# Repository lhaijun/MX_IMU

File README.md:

1. 代码优化：更合理稳定的代码组织结构为了优化数据读取、姿态解算和串口发送的代码结构，同时提升稳定性和可维护性，建议从以下几个方面入手：1.1 任务划分与优先级设计目前你使用 FreeRTOS 的定时器轮询方式，虽然简单，但可能导致任务耦合过高，且实时性难以保证。建议将功能模块拆分为独立的任务，利用 FreeRTOS 的多任务特性来提升代码模块化和稳定性。任务拆分建议：IMU 数据读取任务（高优先级）：负责从 ICM42688P 读取原始数据（加速度、角速度等）。建议使用 SPI/I2C 中断驱动的方式，避免轮询占用 CPU。读取频率可以根据 IMU 的采样率（如 100Hz 或 200Hz）设置。
姿态解算任务（中优先级）：接收 IMU 原始数据，进行姿态解算（如四元数或欧拉角）。可以利用 FreeRTOS 的队列（Queue）或信号量（Semaphore）从 IMU 任务获取数据，避免直接调用。
数据发送任务（低优先级）：负责将解算结果通过串口（UART）以 MAVLink 协议发送到上位机。可以使用另一队列接收姿态解算任务的数据。
命令处理任务（低优先级）：处理上位机通过 MAVLink 协议发送的参数调整命令，更新板载配置。

优先级设置：IMU 读取任务优先级最高，确保数据采集的实时性。
姿态解算次之，保证解算的及时性。
数据发送和命令处理优先级较低，因为串口通信和参数调整对实时性要求较低。

任务通信：使用 FreeRTOS 的 队列（Queue） 传递数据，例如：IMU 任务将原始数据放入队列，姿态解算任务从中读取。
姿态解算任务将结果放入另一个队列，供数据发送任务使用。

如果需要同步，使用 信号量（Semaphore） 或 事件标志（Event Group） 通知任务间状态。

1.2 替换定时器轮询为中断驱动IMU 数据读取：ICM42688P 支持数据就绪中断（Data Ready Interrupt）。建议配置中断引脚，当 IMU 数据准备好时触发中断，在中断服务函数（ISR）中读取数据并存入队列。这样可以避免轮询浪费 CPU 资源。
串口发送：使用 UART 的 DMA 模式发送 MAVLink 数据包，减少 CPU 干预。FreeRTOS 的任务只需将数据写入 DMA 缓冲区，硬件会自动完成发送。
姿态解算：姿态解算任务可以由事件触发（如队列中有新数据时运行），避免固定周期轮询。

1.3 代码模块化分离硬件驱动与应用逻辑：将 ICM42688P 的 SPI/I2C 驱动代码封装为独立模块（如 icm42688p.c/h），提供初始化、数据读取等接口。
姿态解算算法（如 Madgwick 或 Mahony 滤波）封装为单独模块（如 attitude.c/h），输入为 IMU 数据，输出为姿态数据。
MAVLink 协议处理封装为单独模块（如 mavlink_handler.c/h），负责打包和解析数据。

配置文件：将关键参数（如 IMU 采样率、滤波参数、串口波特率）集中在一个配置文件（如 config.h）中，方便上位机调整和代码维护。
错误处理：为每个模块添加错误检测和日志记录（如通过串口输出调试信息），便于调试和排查问题。

1.4 优化 FreeRTOS 资源使用任务栈大小：使用 FreeRTOS 的 uxTaskGetStackHighWaterMark 检查每个任务的栈使用情况，调整栈大小以节省内存。
队列长度：根据数据速率和任务调度频率，合理设置队列长度，避免队列满导致数据丢失。
调度器优化：确保任务调度频率与硬件性能匹配，避免任务抢占导致延迟。例如，IMU 采样率 100Hz，任务调度周期应与之同步。

1.5 示例代码结构以下是一个推荐的 FreeRTOS 任务组织示例：c

#include "FreeRTOS.h"
#include "task.h"
#include "queue.h"
#include "icm42688p.h"
#include "attitude.h"
#include "mavlink_handler.h"

// 队列句柄
QueueHandle_t imu_data_queue, attitude_data_queue;

// IMU 数据读取任务
void imu_read_task(void *pvParameters) {
    while (1) {
        // 假设通过中断触发读取
        imu_data_t data = icm42688p_read();
        xQueueSend(imu_data_queue, &data, portMAX_DELAY);
        vTaskDelay(pdMS_TO_TICKS(10)); // 100Hz
    }
}

// 姿态解算任务
void attitude_task(void *pvParameters) {
    imu_data_t imu_data;
    attitude_data_t attitude;
    while (1) {
        if (xQueueReceive(imu_data_queue, &imu_data, portMAX_DELAY)) {
            attitude = attitude_calculate(&imu_data);
            xQueueSend(attitude_data_queue, &attitude, portMAX_DELAY);
        }
    }
}

// 数据发送任务
void mavlink_send_task(void *pvParameters) {
    attitude_data_t attitude;
    while (1) {
        if (xQueueReceive(attitude_data_queue, &attitude, portMAX_DELAY)) {
            mavlink_send_attitude(&attitude);
        }
    }
}

void main(void) {
    // 初始化硬件和 FreeRTOS
    icm42688p_init();
    mavlink_init();
    
    // 创建队列
    imu_data_queue = xQueueCreate(10, sizeof(imu_data_t));
    attitude_data_queue = xQueueCreate(10, sizeof(attitude_data_t));
    
    // 创建任务
    xTaskCreate(imu_read_task, "IMU", 256, NULL, 3, NULL);
    xTaskCreate(attitude_task, "Attitude", 512, NULL, 2, NULL);
    xTaskCreate(mavlink_send_task, "MAVLink", 256, NULL, 1, NULL);
    
    // 启动调度器
    vTaskStartScheduler();
}

1.6 性能测试与验证实时性测试：使用逻辑分析仪或调试串口记录任务执行时间，确保 IMU 数据读取和姿态解算满足实时性要求。
稳定性测试：长时间运行系统，检查是否有内存泄漏或任务死锁。
数据一致性：验证上位机接收的 MAVLink 数据与板载解算结果一致。

2. 开源文档组织：GitHub 开源准备为了在 GitHub 上开源你的设计和代码，清晰的文档和项目结构是吸引用户和贡献者的关键。以下是建议的文档组织方式和内容：2.1 仓库结构

project_name/
├── docs/                     # 文档目录
│   ├── hardware/             # 硬件相关文档
│   ├── software/             # 软件相关文档
│   └── tutorials/            # 使用教程
├── firmware/                 # 固件代码
│   ├── src/                  # 源代码
│   ├── inc/                  # 头文件
│   └── lib/                  # 第三方库（如 FreeRTOS、MAVLink）
├── hardware/                 # 硬件设计文件
│   ├── schematic/            # 原理图（如 KiCad 文件）
│   ├── pcb/                  # PCB 布局
│   └── bom/                  # 物料清单
├── examples/                 # 示例代码或上位机代码
├── LICENSE                   # 开源许可证（如 MIT、Apache 2.0）
└── README.md                 # 项目主页

2.2 README.md 内容README 是项目的门面，需简洁但信息全面。建议包含以下内容：项目概述：简要介绍项目（STM32F405 + ICM42688P 的 IMU 系统，支持 MAVLink 协议）。
功能特性：IMU 数据读取（加速度、角速度）
姿态解算（四元数/欧拉角）
MAVLink 协议通信
FreeRTOS 实时系统

硬件要求：列出核心硬件（STM32F405、ICM42688P）及其连接方式。
软件依赖：STM32CubeIDE 或其他 IDE
FreeRTOS
MAVLink 库

快速开始：克隆仓库：git clone <repo_url>
硬件连接说明
编译和烧录固件步骤
上位机配置和运行

贡献指南：如何提交 Issue 或 Pull Request。
许可证：明确项目的开源许可证。
联系方式：可选，提供邮箱或社区链接。

2.3 文档内容硬件文档（docs/hardware/）：原理图和 PCB 设计说明（推荐使用 KiCad 或 Eagle）。
物料清单（BOM），包括元件型号和供应商链接。
硬件连接说明（如 SPI/I2C 引脚分配）。

软件文档（docs/software/）：代码架构说明（任务划分、模块功能）。
MAVLink 协议实现细节（支持的消息类型、参数调整流程）。
姿态解算算法说明（如 Madgwick 滤波的原理和参数）。

使用教程（docs/tutorials/）：固件烧录教程（使用 ST-Link 或其他工具）。
上位机配置和运行说明。
参数调整示例（如通过 MAVLink 修改滤波增益）。

API 文档（可选）：如果代码模块化程度高，可使用 Doxygen 生成 API 文档。

2.4 开源注意事项选择许可证：推荐 MIT 或 Apache 2.0，简单且适合硬件/软件开源。确保在仓库根目录添加 LICENSE 文件。
代码注释：确保代码有清晰的注释，尤其是关键模块（如 IMU 驱动、姿态解算）。
版本管理：使用 Git 提交规范（如 feat: add IMU driver），并定期发布版本（Releases）。
测试用例：提供简单的测试代码或脚本，帮助用户验证硬件和固件功能。
社区互动：在 README 中添加 GitHub Issues 模板，鼓励用户反馈问题或贡献代码。

2.5 示例 README 片段markdown

# STM32F405 + ICM42688P IMU Project

A FreeRTOS-based IMU system using STM32F405 and ICM42688P, with MAVLink protocol support for attitude calculation and data communication.

## Features
- High-frequency IMU data acquisition (100Hz+)
- Real-time attitude calculation (quaternion/Euler angles)
- MAVLink protocol for PC communication
- Configurable parameters via MAVLink

## Getting Started
1. Clone the repository:
   ```bash
   git clone https://github.com/yourusername/project_name

Connect STM32F405 and ICM42688P via SPI/I2C (see docs/hardware/).
Build and flash firmware using STM32CubeIDE.
Run the provided PC application to receive MAVLink data.

LicenseMIT License

---

### 3. 其他建议
- **硬件优化**：
  - 检查 ICM42688P 的电源和信号完整性，确保数据读取稳定。
  - 如果可能，添加外部晶振以提高 STM32F405 的时钟精度。
- **上位机完善**：
  - 在上位机中添加数据可视化功能（如姿态 3D 模型）。
  - 提供 MAVLink 参数调整的 GUI 界面，方便用户操作。
- **开源社区推广**：
  - 在 X 或其他技术社区分享你的项目，吸引开发者参与。
  - 考虑制作一个简单的演示视频，展示硬件运行效果。

---

### 总结
- **代码优化**：将功能拆分为 FreeRTOS 任务（IMU 读取、姿态解算、数据发送），使用中断驱动和队列通信，模块化代码结构。
- **文档组织**：在 GitHub 上创建清晰的目录结构，编写详细的 README 和模块化文档，选择合适的许可证。

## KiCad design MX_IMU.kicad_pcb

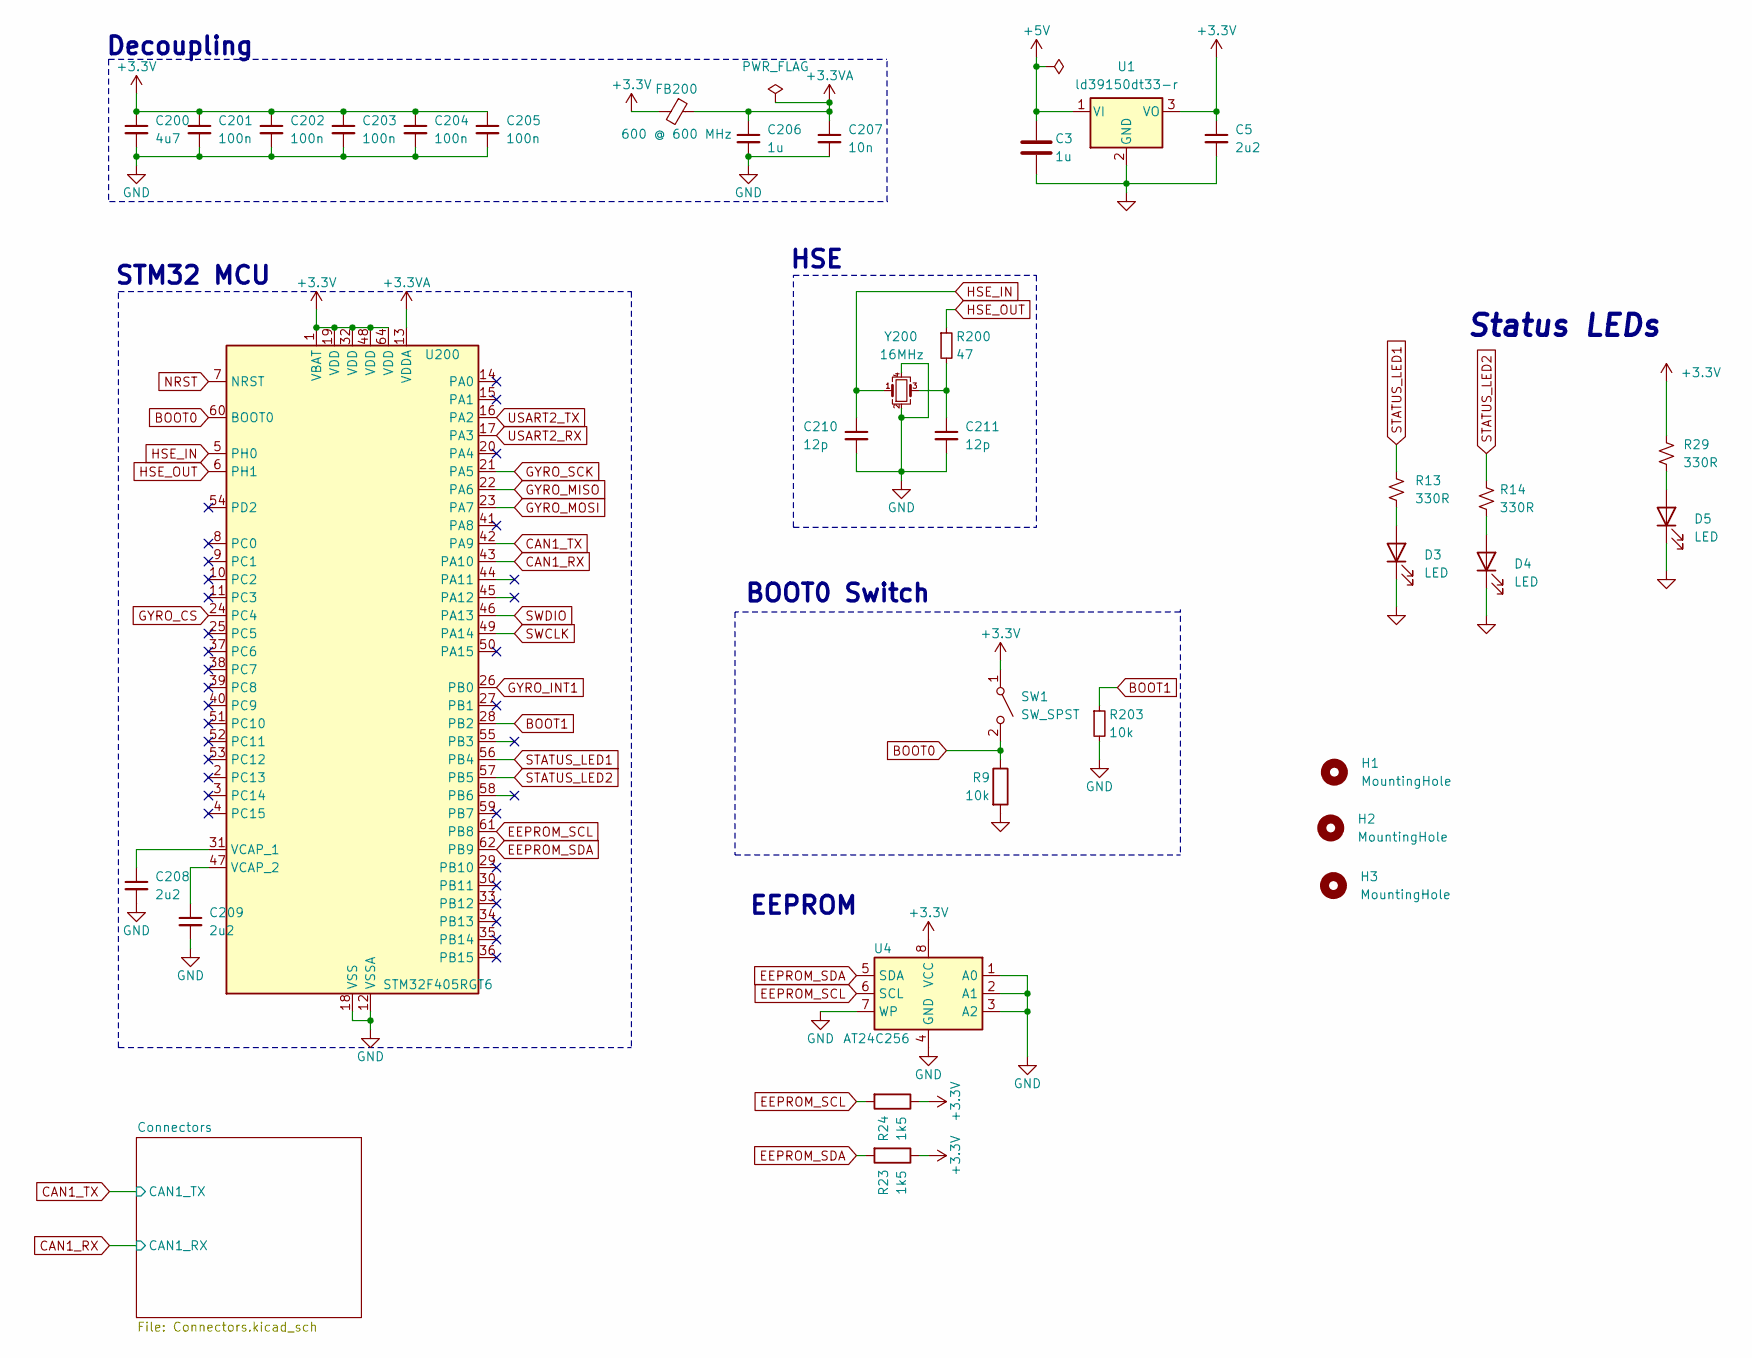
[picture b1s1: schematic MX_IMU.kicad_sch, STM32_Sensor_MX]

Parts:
C3: 1u; C_0603_1608Metric
C5, C208, C209: 2u2; C_0603_1608Metric; LCSC Part # C23630
C200: 4u7; C_0603_1608Metric; LCSC Part # C19666
C201, C202, C203, C204, C205: 100n; C_0402_1005Metric; LCSC Part # C1525
C206: 1u; C_0402_1005Metric; LCSC Part # C52923
C207: 10n; C_0402_1005Metric; LCSC Part # C15195
C210, C211: 12p; C_0402_1005Metric; LCSC Part # C1547
D3, D4, D5: LED; LED_0402_1005Metric
FB200: 600 @ 600 MHz; L_0805_2012Metric; LCSC Part # C1017
H1, H2, H3: MountingHole; MountingHole_2mm
R9: 10k; R_0603_1608Metric
R13, R14, R29: 330R; R_0402_1005Metric
R23, R24: 1k5; R_0805_2012Metric_Pad1.20x1.40mm_HandSolder
R200: 47; R_0402_1005Metric; LCSC Part # C25118
R203: 10k; R_0402_1005Metric; LCSC Part # C25744
SW1: SW_SPST; SW_SPST_B3U-3000P-B
U1: ld39150dt33-r; to-252-2_dpak-2-leg; Manufacturer Part Number LD39150DT33-R
U4: AT24C256; SOIC-8_3.9x4.9mm_P1.27mm; LCSC C6482
U200: STM32F405RGT6; LQFP-64_10x10mm_P0.5mm; LCSC Part # C15742
Y200: 16MHz; Crystal_SMD_3225-4Pin_3.2x2.5mm; LCSC Part # C13738

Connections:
+3.3V: C5.1, C200.1, C201.1, C202.1, C203.1, C204.1, C205.1, FB200.2, R23.1, R24.1, R29.1, SW1.1 (A), U1.3 (VO), U4.8 (VCC), U200.1 (VBAT), U200.19 (VDD), U200.32 (VDD), U200.48 (VDD), U200.64 (VDD); also elsewhere on the board
+3.3VA: C206.1, C207.1, FB200.1, U200.13 (VDDA)
+5V: C3.1, U1.1 (VI); also elsewhere on the board
BOOT0: R9.1, SW1.2 (B), U200.60 (BOOT0)
BOOT1: R203.1, U200.28 (PB2)
CAN1_RX: U200.43 (PA10); also elsewhere on the board
CAN1_TX: U200.42 (PA9); also elsewhere on the board
EEPROM_SCL: R24.2, U4.6 (SCL), U200.61 (PB8)
EEPROM_SDA: R23.2, U4.5 (SDA), U200.62 (PB9)
GND: C3.2, C5.2, C200.2, C201.2, C202.2, C203.2, C204.2, C205.2, C206.2, C207.2, C208.2, C209.2, C210.2, C211.2, D3.1 (K), D4.1 (K), D5.1 (K), R9.2, R203.2, U1.2 (GND), U4.1 (A0), U4.2 (A1), U4.3 (A2), U4.4 (GND), U4.7 (WP), U200.12 (VSSA), U200.18 (VSS), U200.63 (VSS), Y200.2, Y200.4; also elsewhere on the board
GYRO_CS: U200.24 (PC4); also elsewhere on the board
GYRO_INT1: U200.26 (PB0); also elsewhere on the board
GYRO_MISO: U200.22 (PA6); also elsewhere on the board
GYRO_MOSI: U200.23 (PA7); also elsewhere on the board
GYRO_SCK: U200.21 (PA5); also elsewhere on the board
HSE_IN: C210.1, U200.5 (PH0), Y200.1
HSE_OUT: R200.1, U200.6 (PH1)
NRST: U200.7 (NRST); also elsewhere on the board
unnamed: C211.1, R200.2, Y200.3
unnamed: D3.2 (A), R13.2
unnamed: D4.2 (A), R14.2
unnamed: D5.2 (A), R29.2
unnamed: C208.1, U200.31 (VCAP_1)
unnamed: C209.1, U200.47 (VCAP_2)
STATUS_LED1: R13.1, U200.56 (PB4)
STATUS_LED2: R14.1, U200.57 (PB5)
SWCLK: U200.49 (PA14); also elsewhere on the board
SWDIO: U200.46 (PA13); also elsewhere on the board
USART2_RX: U200.17 (PA3); also elsewhere on the board
USART2_TX: U200.16 (PA2); also elsewhere on the board

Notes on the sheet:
HSE
Status LEDs
STM32 MCU
BOOT0 Switch
EEPROM
Decoupling

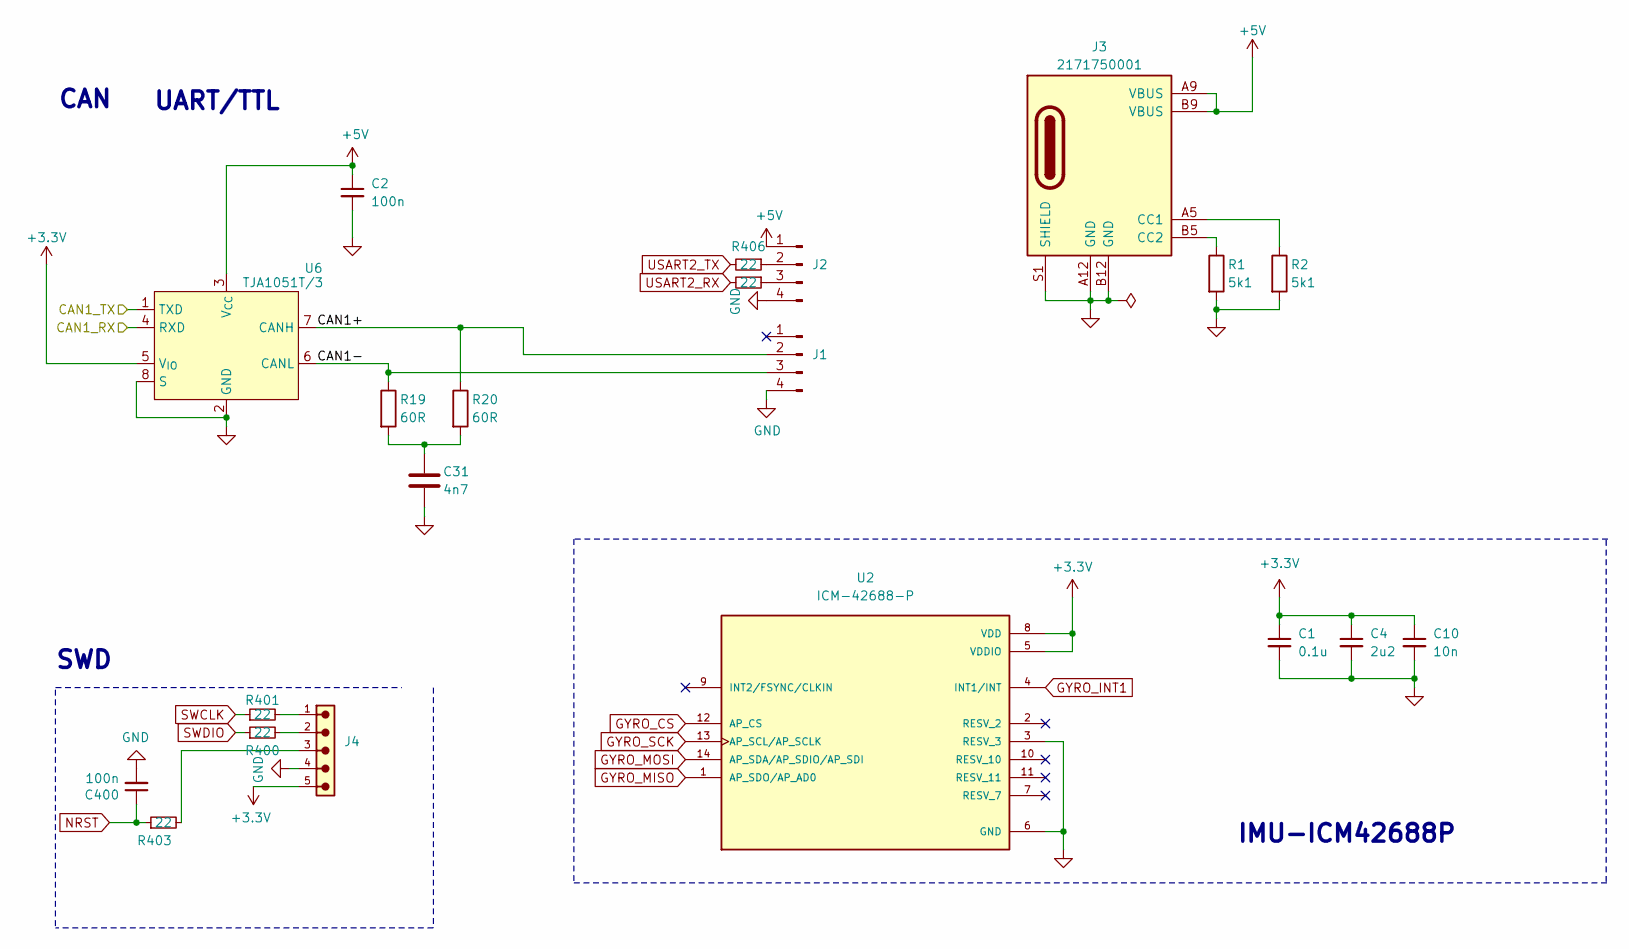
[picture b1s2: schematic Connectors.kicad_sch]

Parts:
C1: 0.1u; C_0402_1005Metric
C2, C400: 100n; C_0402_1005Metric; LCSC Part # C1525
C4: 2u2; C_0603_1608Metric; LCSC Part # C23630
C10: 10n; C_0201_0603Metric
C31: 4n7; C_0603_1608Metric
J1, J2: KH-1.27PH180-1X4P-L7.2; PinHeader_1x04_P1.27mm_Vertical
J3: 2171750001; molex_2171750001_usb_c_6p; Manufacturer Part Number 2171750001
J4: ZX-PZ2.54-1-5PZZ; CONN-HEADER-VERT-5POS-2.54MM
R1, R2: 5k1; R_0603_1608Metric
R19, R20: 60R; R_0603_1608Metric
R400, R401, R403, R406, R407: 22; R_0402_1005Metric; LCSC Part # C25092
U2: ICM-42688-P; PQFN50P300X250X97-14N; PARTREV 1.2
U6: TJA1051T/3; sot96-1_soic-8; Manufacturer Part Number TJA1051T/3

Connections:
+3.3V: C1.1, C4.1, C10.1, J4.5, U2.5 (VDDIO), U2.8 (VDD), U6.5 (V_{IO}); also elsewhere on the board
+5V: C2.1, J2.1, J3.A9 (VBUS), J3.B9 (VBUS), U6.3 (V_{CC}); also elsewhere on the board
/Connectors/CAN1+: J1.2, R20.1, U6.7 (CANH)
/Connectors/CAN1-: J1.3, R19.1, U6.6 (CANL)
CAN1_RX: U6.4 (RXD); also elsewhere on the board
CAN1_TX: U6.1 (TXD); also elsewhere on the board
GND: C1.2, C2.2, C4.2, C10.2, C31.2, C400.2, J1.4, J2.4, J3.A12 (GND), J3.B12 (GND), J3.S1 (SHIELD), J4.4, R1.2, R2.2, U2.3 (RESV_3), U2.6 (GND), U6.2 (GND), U6.8 (S); also elsewhere on the board
GYRO_CS: U2.12 (AP_CS); also elsewhere on the board
GYRO_INT1: U2.4 (INT1/INT); also elsewhere on the board
GYRO_MISO: U2.1 (AP_SDO/AP_AD0); also elsewhere on the board
GYRO_MOSI: U2.14 (AP_SDA/AP_SDIO/AP_SDI); also elsewhere on the board
GYRO_SCK: U2.13 (AP_SCL/AP_SCLK); also elsewhere on the board
NRST: C400.1, R403.1; also elsewhere on the board
unnamed: C31.1, R19.2, R20.2
unnamed: J2.2, R406.1
unnamed: J2.3, R407.1
unnamed: J3.A5 (CC1), R2.1
unnamed: J3.B5 (CC2), R1.1
unnamed: J4.1, R401.2
unnamed: J4.2, R400.2
unnamed: J4.3, R403.2
SWCLK: R401.1; also elsewhere on the board
SWDIO: R400.1; also elsewhere on the board
USART2_RX: R407.2; also elsewhere on the board
USART2_TX: R406.2; also elsewhere on the board

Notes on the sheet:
SWD
IMU-ICM42688P
CAN
UART/TTL

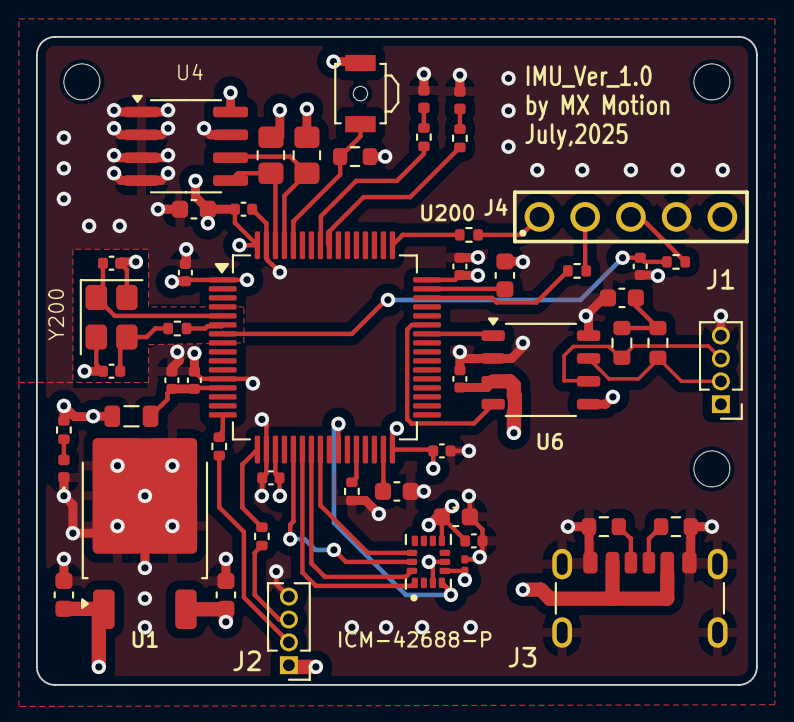
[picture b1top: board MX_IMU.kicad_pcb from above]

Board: 4 copper layers, 40.0 x 36.0 mm, 55 parts (0 on the bottom side), 40 nets.

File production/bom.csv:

Designator,Footprint,Quantity,Value,LCSC Part #
C1,0402,1,0.1u,
C10,0201,1,10n,
"C2, C201, C202, C203, C204, C205, C400",0402,7,100n,C1525
C200,0603,1,4u7,C19666
C206,0402,1,1u,C52923
C207,0402,1,10n,C15195
"C208, C209, C4, C5",0603,4,2u2,C23630
"C210, C211",0402,2,12p,C1547
C3,0603,1,1u,
C31,0603,1,4n7,
"D3, D4, D5",0402,3,LED,
FB200,0805,1,600 @ 600 MHz,C1017
"J1, J2",PinHeader_1x04_P1.27mm_Vertical,2,KH-1.27PH180-1X4P-L7.2,
J3,molex_2171750001_usb_c_6p,1,2171750001,
J4,CONN-HEADER-VERT-5POS-2.54MM,1,ZX-PZ2.54-1-5PZZ,
"R1, R2",0603,2,5k1,
"R13, R14, R29",0402,3,330R,
"R19, R20",0603,2,60R,
R200,0402,1,47,C25118
R203,0402,1,10k,C25744
"R23, R24",0805,2,1k5,
"R400, R401, R403, R406, R407",0402,5,22,C25092
R9,0603,1,10k,
SW1,SW_SPST_B3U-3000P-B,1,SW_SPST,
U1,to-252-2_dpak-2-leg,1,ld39150dt33-r,
U2,PQFN50P300X250X97-14N,1,ICM-42688-P,
U200,LQFP-64_10x10mm_P0.5mm,1,STM32F405RGT6,C15742
U4,SOIC-8_3.9x4.9mm_P1.27mm,1,AT24C256,C6482
U6,sot96-1_soic-8,1,TJA1051T/3,
Y200,Crystal_SMD_3225-4Pin_3.2x2.5mm,1,16MHz,C13738

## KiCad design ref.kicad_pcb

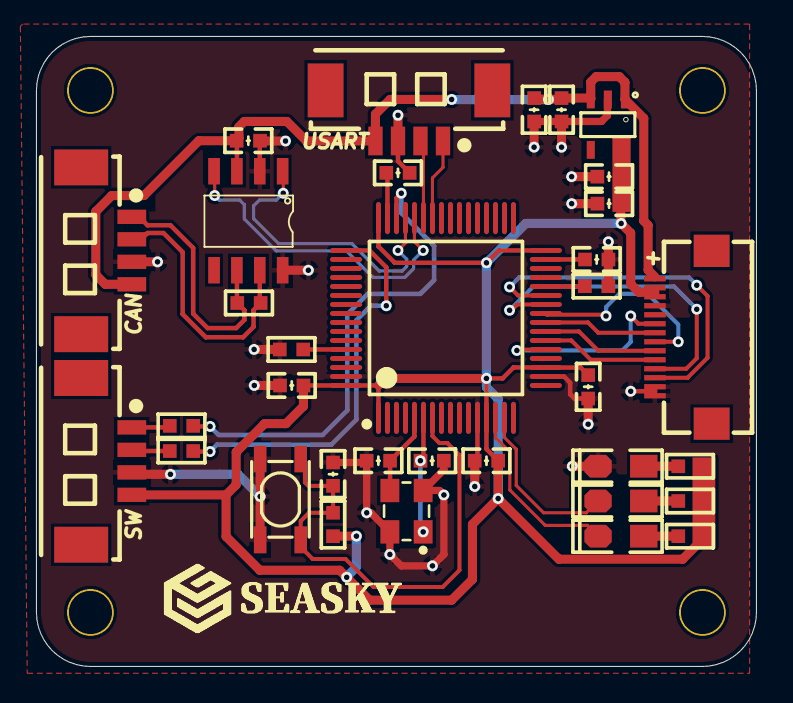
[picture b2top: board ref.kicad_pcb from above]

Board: 2 copper layers, 40.0 x 35.0 mm, 35 parts (0 on the bottom side), 32 nets.

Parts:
C3, C12, C13, C15, C16, C18, C19: 0.1uF; C 0603_L
C8, C17: 2.2uF; C 0603_L
C9, C10: 22pF; C 0603_L
C11, C14: 10uF; C 0603_L
CAN1: HDR-1X4; MX 1.25-WS-4P
Designator3236: Comment; SEASKY1
FPC2: FPC14; FPC-SMD_P0.50-14P_QCHF-SM-H2.0
J1: TJA1050; SOIC-8_150mil
LED1: 红色; LED 0805R
LED2, LED3: 红色; LED 0805G
R1, R2, R3: 4.7K; R 0603_L
R6, R10, R11: 10K; R 0603_L
R8, R9: 0R; R 0603_L
R12: 120R; R 0603_L
RST1: RES; SMD-3.2*4.2
SW1: HDR-1X4; MX 1.25-WS-4P
U3: STM32F405RGT6; LQFP-64_10X10X05P
U4: RT9013-33GB; SOT23-5L
UART1: HDR-1X4; MX 1.25-WS-4P
Y1: 12MHz; SMD-3225_4P

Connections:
CAN1_RX(PA11): J1.4, U3.44
CAN1_TX(PA12): J1.1, U3.45
CAN_H: CAN1.2, J1.7, R12.1
CAN_L: CAN1.1, J1.6, R12.2
CSB1_ACC(PC4): FPC2.8, U3.24
CSB2_GYRO(PC5): FPC2.7, U3.25
GNDS: C3.1, C8.1, C9.1, C10.2, C11.1, C12.1, C13.1, C14.1, C15.1, C16.1, C17.1, C18.1, C19.2, CAN1.3, FPC2.1, FPC2.2, FPC2.10, FPC2.11, J1.2, J1.8, LED1.2, R6.2, R11.1, RST1.2, SW1.3, U3.12, U3.18, U3.63, U4.2, UART1.3, Y1.2, Y1.4
INT1_ACCEL(PB0): FPC2.4, U3.26
INT3_GYRO(PB1): FPC2.3, U3.27
LED1(PA0): LED2.2, U3.14
LED2(PA1): LED3.2, U3.15
NRST: C16.2, R10.1, RST1.1, U3.7
NetC8_2: C8.2, U3.47
NetC9_2: C9.2, U3.6, Y1.1
NetC10_1: C10.1, U3.5, Y1.3
NetC17_2: C17.2, U3.31
NetLED1_1: LED1.1, R1.1
NetLED2_1: LED2.1, R2.1
NetLED3_1: LED3.1, R3.1
NetR6_1: R6.1, U3.60
NetR8_2: R8.2, SW1.1
NetR9_2: R9.2, SW1.2
NetR11_2: R11.2, U3.28
SPI1_MISO(PA6): FPC2.5, U3.22
SPI1_MOSI(PA7): FPC2.6, U3.23
SPI1_SCK(PA5): FPC2.9, U3.21
SWCLK(PA14): R9.1, U3.49
SWDIO(PA13): R8.1, U3.46
USART1_RX(PA10): U3.43, UART1.2
USART1_TX(P9): U3.42, UART1.1
VCC3V3S: C3.2, C13.2, C14.2, C15.2, C18.2, FPC2.12, FPC2.13, R1.2, R2.2, R3.2, R10.2, SW1.4, U3.1, U3.13, U3.19, U3.32, U3.48, U3.64, U4.5
VCC5VS: C11.2, C12.2, C19.1, CAN1.4, FPC2.14, J1.3, U4.1, U4.3, UART1.4

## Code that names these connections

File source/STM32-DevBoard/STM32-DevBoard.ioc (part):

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Mcu.Name=STM32F405RGTx
Mcu.Package=LQFP64
Mcu.UserName=STM32F405RGTx
PA10.Mode=Asynchronous
PA10.Signal=USART1_RX
PA13.Mode=Trace_Asynchronous_SW
PA13.Signal=SYS_JTMS-SWDIO
PA14.Mode=Trace_Asynchronous_SW
PA14.Signal=SYS_JTCK-SWCLK
PA2.GPIOParameters=GPIO_ModeDefaultPP,GPIO_Label
PA2.GPIO_Label=USART2_TX 
PA2.GPIO_ModeDefaultPP=GPIO_MODE_AF_PP
PA2.Mode=Asynchronous
PA2.Signal=USART2_TX
PA3.GPIOParameters=GPIO_ModeDefaultPP,GPIO_Label
PA3.GPIO_Label=USART2_RX
PA3.GPIO_ModeDefaultPP=GPIO_MODE_AF_PP
PA3.Mode=Asynchronous
PA3.Signal=USART2_RX
PA4.Signal=GPIO_Output
PA5.GPIOParameters=GPIO_Label
PA5.GPIO_Label=IMU_CLK
PA5.Mode=Full_Duplex_Master
PA5.Signal=SPI1_SCK
PA6.GPIOParameters=GPIO_Label
PA6.GPIO_Label=IMU_MISO
PA6.Mode=Full_Duplex_Master
PA6.Signal=SPI1_MISO
PA7.GPIOParameters=GPIO_Label
PA7.GPIO_Label=IMU_MOSI
PA7.Mode=Full_Duplex_Master
PA7.Signal=SPI1_MOSI
PA9.Mode=Asynchronous
PA9.Signal=USART1_TX
PB0.GPIOParameters=GPIO_Label,GPIO_ModeDefaultEXTI
PB0.GPIO_Label=IMU_INT1
PB0.GPIO_ModeDefaultEXTI=GPIO_MODE_IT_RISING_FALLING
PB0.Signal=GPXTI0
PB3.Mode=Trace_Asynchronous_SW
PB3.Signal=SYS_JTDO-SWO
PB4.GPIOParameters=GPIO_Label
PB4.GPIO_Label=Status_LED1
PB4.Signal=GPIO_Output
PB5.GPIOParameters=GPIO_Label
PB5.GPIO_Label=Status_LED2
PB5.Signal=GPIO_Output
PC4.GPIOParameters=GPIO_Label
PC4.GPIO_Label=IMU_CS
PC4.Signal=GPIO_Output
PH0-OSC_IN.Mode=HSE-External-Oscillator
PH0-OSC_IN.Signal=RCC_OSC_IN
PH1-OSC_OUT.Mode=HSE-External-Oscillator
PH1-OSC_OUT.Signal=RCC_OSC_OUT
RCC.HSE_VALUE=16000000
RCC.SYSCLKFreq_VALUE=168000000
RCC.SYSCLKSource=RCC_SYSCLKSOURCE_PLLCLK
board=custom

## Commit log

2025-06-17 Move to github
2025-06-18 add usb and clean up
2025-06-23 add mounting hole
2025-06-25 add mountinghole in sch
2025-06-26 update bom
2025-07-01 Cleanup and check on JCLPCB
2025-07-04 Remove vias around Y200 and IMU
2025-07-07 add coper ground and other design
2025-07-08 Version for JLCPCB
2025-08-21 Add firmware source
2025-08-28 AHRS and Mavlink
